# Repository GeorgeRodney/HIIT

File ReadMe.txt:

To Debug:
    - Flash it and have program running with stlink attached
    - open OPENODC: openocd -f interface/stlink.cfg -f target/stm32f4x.cfg
    - new terminal: gdb-multiarch build/Timer.elf
    - target extended-remote :3333
    - Add breakpoints and go

TODO:
    [D]: Make correct alternating SPRINT/REST Play sequence. 
    [D]: Add functionality to set seconds for SPRINT with butttons.
    []: Create seconds sound so the user knows where they are in the logic structure.
    []: Create a schematic on EasyEda
    []: Create Sound functions to replace // Announce comments
    []: Remove delay from PlayBuzzer()

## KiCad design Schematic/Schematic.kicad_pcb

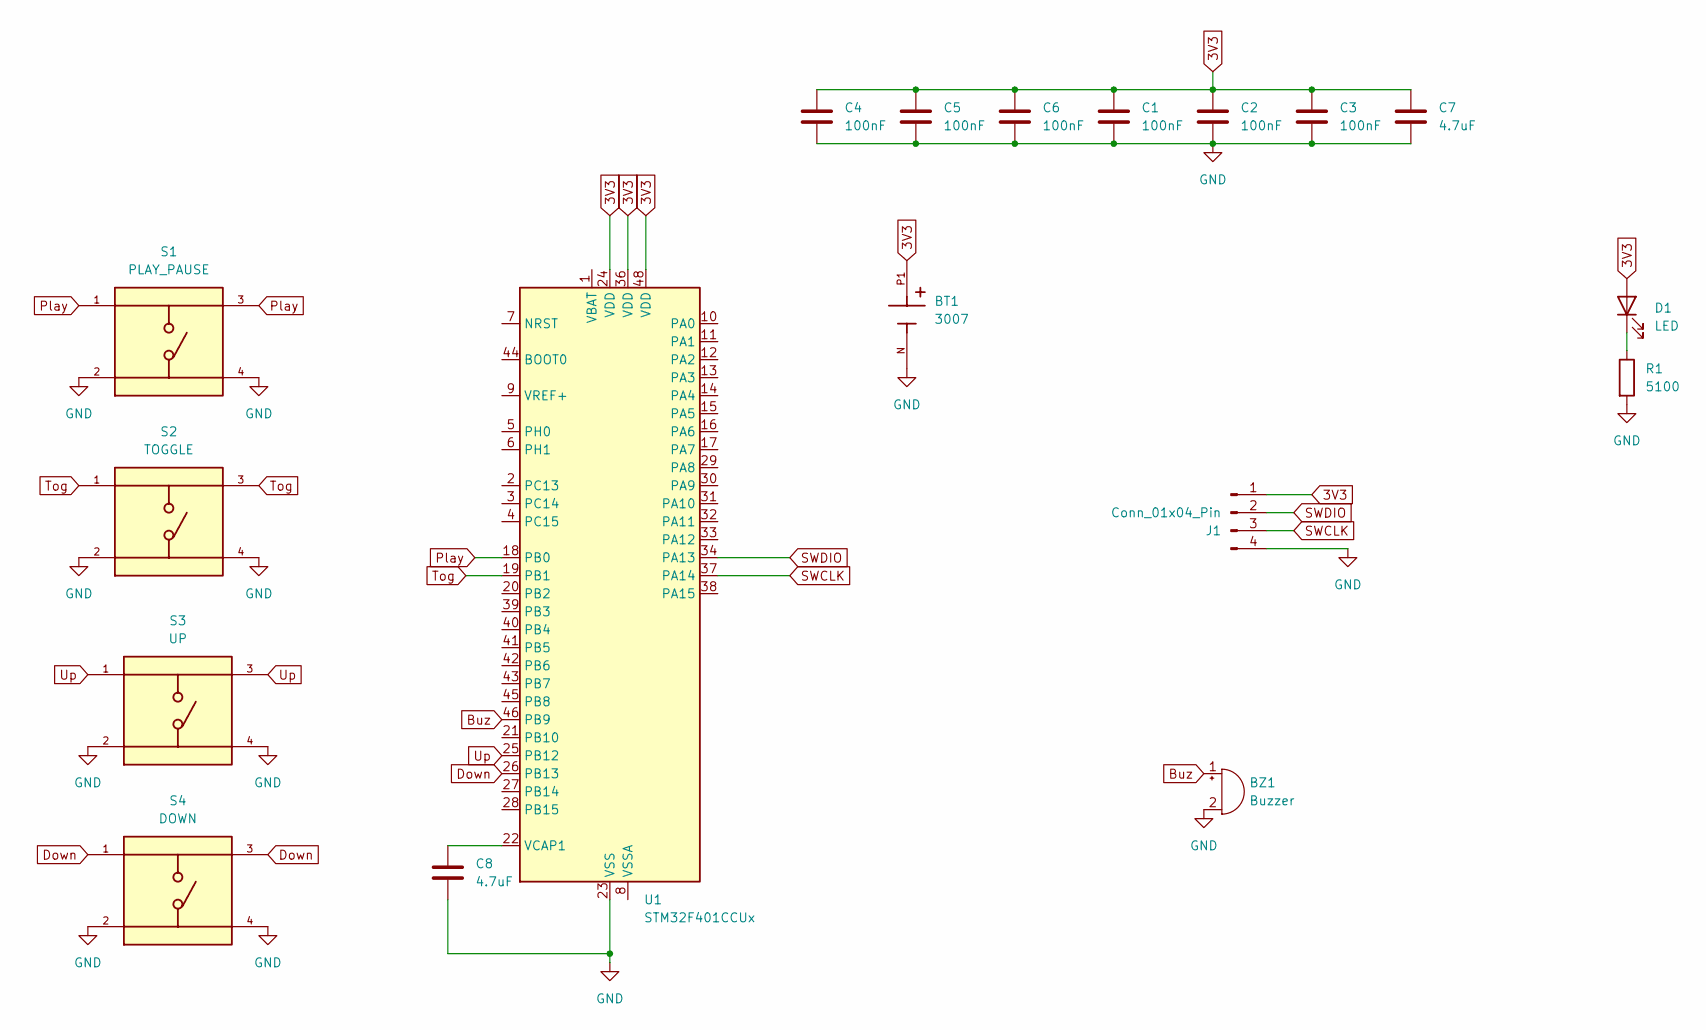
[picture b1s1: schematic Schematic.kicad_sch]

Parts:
BT1: 3007; BAT_3007; PARTREV M
BZ1: Buzzer; Buzzer_Mallory_AST1240MLQ
C1, C2, C3, C4, C5, C6: 100nF; C_0201_0603Metric
C7, C8: 4.7uF; C_0201_0603Metric
D1: LED; LED_0201_0603Metric
J1: Conn_01x04_Pin; PinHeader_1x04_P2.54mm_Horizontal
R1: 5100; R_0201_0603Metric
S1: PLAY_PAUSE; SW_TS04-66-73-BK-100-SMT; PARTREV 1.0
S2: TOGGLE; SW_TS04-66-73-BK-100-SMT; PARTREV 1.0
S3: UP; SW_TS04-66-73-BK-100-SMT; PARTREV 1.0
S4: DOWN; SW_TS04-66-73-BK-100-SMT; PARTREV 1.0
U1: STM32F401CCUx; QFN-48-1EP_7x7mm_P0.5mm_EP5.6x5.6mm

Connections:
3V3: BT1.P1, C1.1, C2.1, C3.1, C4.1, C5.1, C6.1, C7.1, D1.2 (A), J1.1, U1.24 (VDD), U1.36 (VDD), U1.48 (VDD)
Buz: BZ1.1 (+), U1.46 (PB9)
Down: S4.1, S4.3, U1.26 (PB13)
GND: BT1.N, BZ1.2 (-), C1.2, C2.2, C3.2, C4.2, C5.2, C6.2, C7.2, C8.2, J1.4, R1.2, S1.2, S1.4, S2.2, S2.4, S3.2, S3.4, S4.2, S4.4, U1.23 (VSS), U1.35 (VSS), U1.47 (VSS), U1.49 (VSS)
unnamed: D1.1 (K), R1.1
unnamed: C8.1, U1.22 (VCAP1)
Play: S1.1, S1.3, U1.18 (PB0)
SWCLK: J1.3, U1.37 (PA14)
SWDIO: J1.2, U1.34 (PA13)
Tog: S2.1, S2.3, U1.19 (PB1)
Up: S3.1, S3.3, U1.25 (PB12)

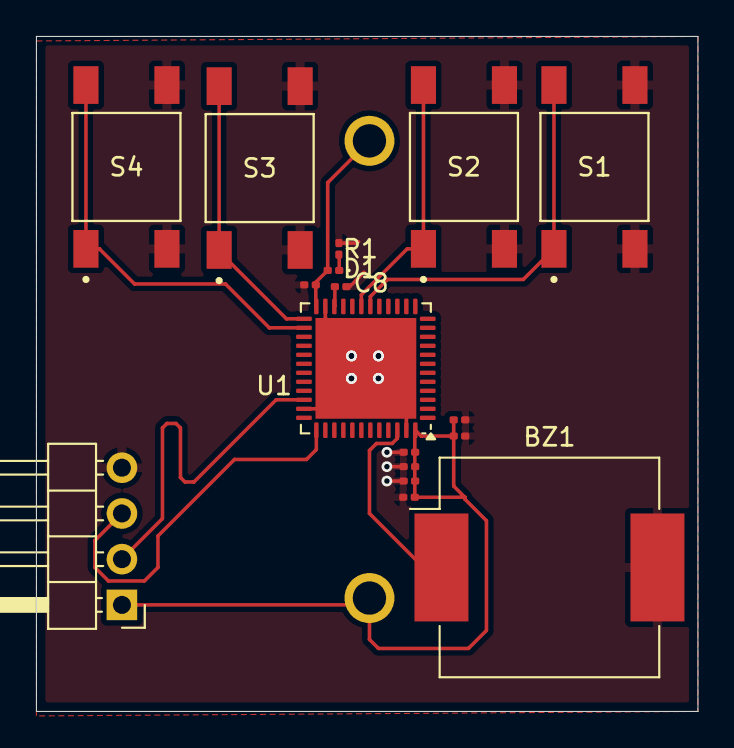
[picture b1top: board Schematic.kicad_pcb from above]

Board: 2 copper layers, 36.8 x 37.5 mm, 18 parts (1 on the bottom side), 11 nets.

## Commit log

2024-12-31 Init
2024-12-31 Cleaned
2024-12-31 Do it
2024-12-31 Added CPP functionality
2024-12-31 PWM working. PLAY state working
2024-12-31 surmthin
2024-12-31 UART defined
2024-12-31 UART working now
2024-12-31 Rough draft play logic
2024-12-31 Added write functions
2025-01-01 Writing to UART is F ing with my logic
2025-01-01 First attempt to have multiple beeps
2025-01-01 Alternating timing thingy working
2025-01-01 Added Toggle and Increment and Decrement functionality
2025-01-02 All 4 buttons working. User can change the timing
2025-01-02 Added Schematic
2025-01-11 gitignore
2025-01-11 Stuf
2025-01-11 Debugging totalSprintTime_
2025-01-11 FIXED
2025-01-11 Schematic stuff
